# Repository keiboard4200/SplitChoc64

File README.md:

# SplitChoc64

SplitChoc64 is a 64-key split low-profile keyboard project built around Seeed XIAO nRF52840 and ZMK.

This repository contains firmware/software, PCB design, mechanical/3D-print data, manufacturing outputs, and project documentation.

## Repository layout

```text
SplitChoc64/
├─ hardware/                 # PCB, case, plate, trackball mechanical data and manufacturing files
│  ├─ main-pcb/
│  │  ├─ Ver000/
│  │  └─ Ver001/
│  └─ trackball-addon/
├─ software/                 # ZMK build/config/module source and archived firmware variants
│  ├─ build.yaml
│  ├─ west.yml
│  ├─ zmk-module/            # active Ver001 ZMK module
│  ├─ firmware/
│  │  ├─ joystick/           # legacy Ver000/2765 implementation
│  │  └─ trackball/          # Ver001 PAW3222 documentation
│  └─ tools/
├─ docs/                     # Project documentation
├─ archive/                  # Historical/original import data
├─ DEVELOPMENT/              # Development snapshots retained for traceability
├─ zephyr/module.yml         # Zephyr entry point redirecting to software/zmk-module
├─ .github/                  # GitHub Actions
└─ README.md
```

## Hardware baseline

- **Ver000**: first manufactured SplitChoc64 production hardware baseline (legacy internal name: Ver012).
- **Ver001**: current manufactured hardware/firmware baseline, stored under `hardware/main-pcb/Ver001/`.
- Kailh Choc V2 hot-swap switches.
- Seeed XIAO nRF52840 Plus on both halves.

## Active Ver001 pointing device

Ver001 uses the RIGHT-side PAW3222 trackball through the PCB-mounted 6-pin FFC interface. The active ZMK module under `software/zmk-module/` is configured for this hardware.

The older 2765 analog-joystick implementation is retained only as a legacy reference under `software/firmware/joystick/`; it is not compiled into the active Ver001 firmware.

Detailed Ver001 trackball wiring and firmware notes are in `software/firmware/trackball/README.md`.

## ZMK build

GitHub Actions reads:

- Build matrix: `software/build.yaml`
- West/config path: `software/`
- SplitChoc64 Zephyr/ZMK module: `software/zmk-module/`

`zephyr/module.yml` remains at repository root because ZMK/Zephyr module discovery expects the module entry point there. The implementation is organized under `software/`.

## Firmware identity

- Shield: `splitchoc64_left` / `splitchoc64_right`
- RIGHT: Central / USB-BLE host / PAW3222 trackball
- LEFT: Peripheral
- Bluetooth name: `SplitChoc64`
- ZMK Studio: retained
- `settings_reset` build: retained

## Validation status

GitHub Actions validates LEFT, RIGHT, and `settings_reset` builds. Physical PAW3222 direction, CPI and feel must still be tuned on the assembled Ver001 hardware.

## License

See the license files and upstream component licenses included with each subproject before redistribution or commercial use.

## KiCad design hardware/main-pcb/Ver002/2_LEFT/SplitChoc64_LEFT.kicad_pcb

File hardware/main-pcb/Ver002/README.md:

# SplitChoc64 Ver002

Clean GitHub source promoted from the user-reviewed XIAO nRF52840 Plus correction.

- `0_COMMON`: shared footprints / 3D assets
- `1_RIGHT`: RIGHT KiCad project + ERC/DRC reports
- `2_LEFT`: LEFT KiCad project + ERC/DRC reports
- `3_PLATE`: accepted TopPlate STEP files
- `4_CASE`: accepted BottomCase / BatteryLid / trackball mechanical STEP files
- Manufacturing exports are intentionally not carried forward from Ver001; regenerate them from Ver002 when needed.

Validation confirmed by the user in KiCad 9.0 before promotion: LEFT/RIGHT ERC 0/0 and DRC 0/0.

Ver002 corrects XIAO nRF52840 Plus pads 28/29, removes unverified pads 30/31, preserves the project-specific front-side solder access pads 32/33, and leaves Ver001 unchanged as historical source.

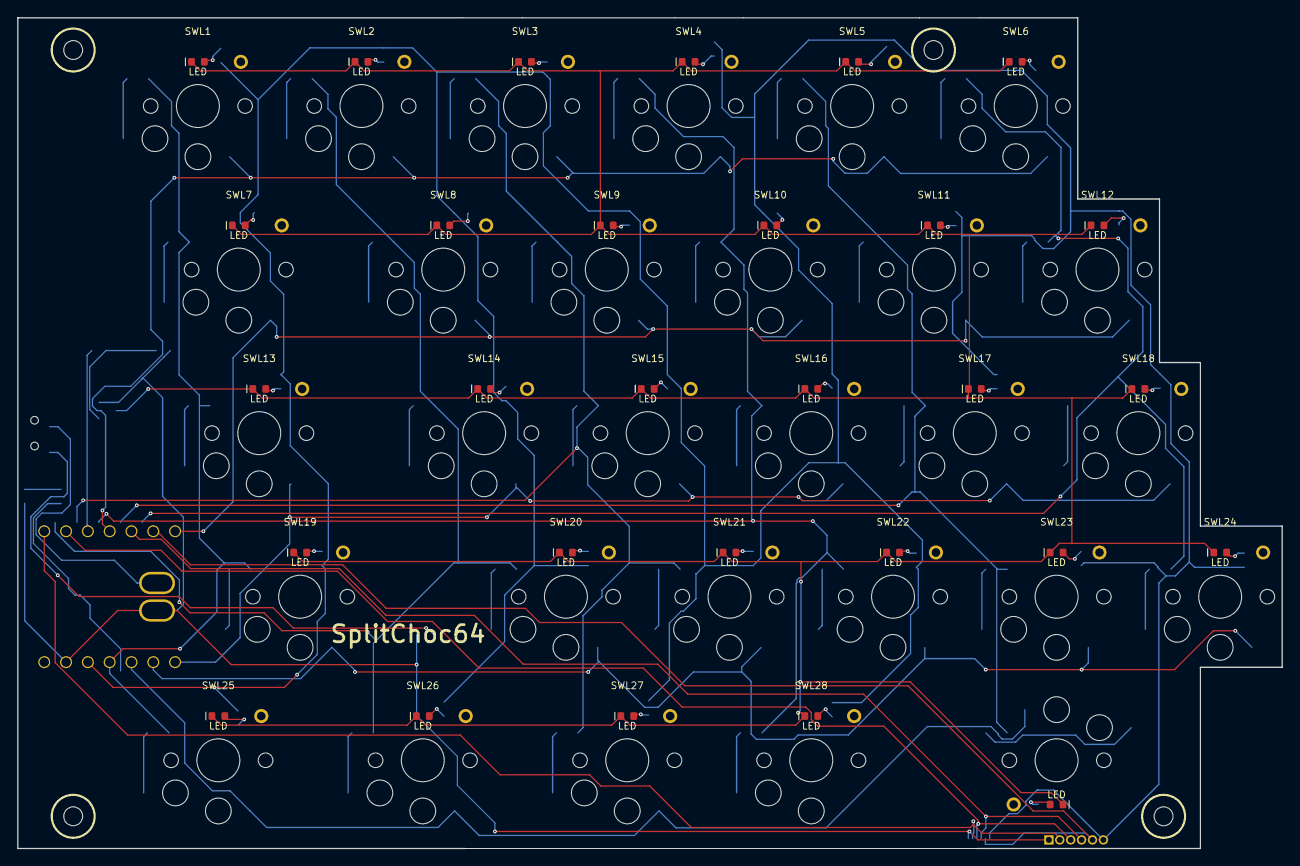
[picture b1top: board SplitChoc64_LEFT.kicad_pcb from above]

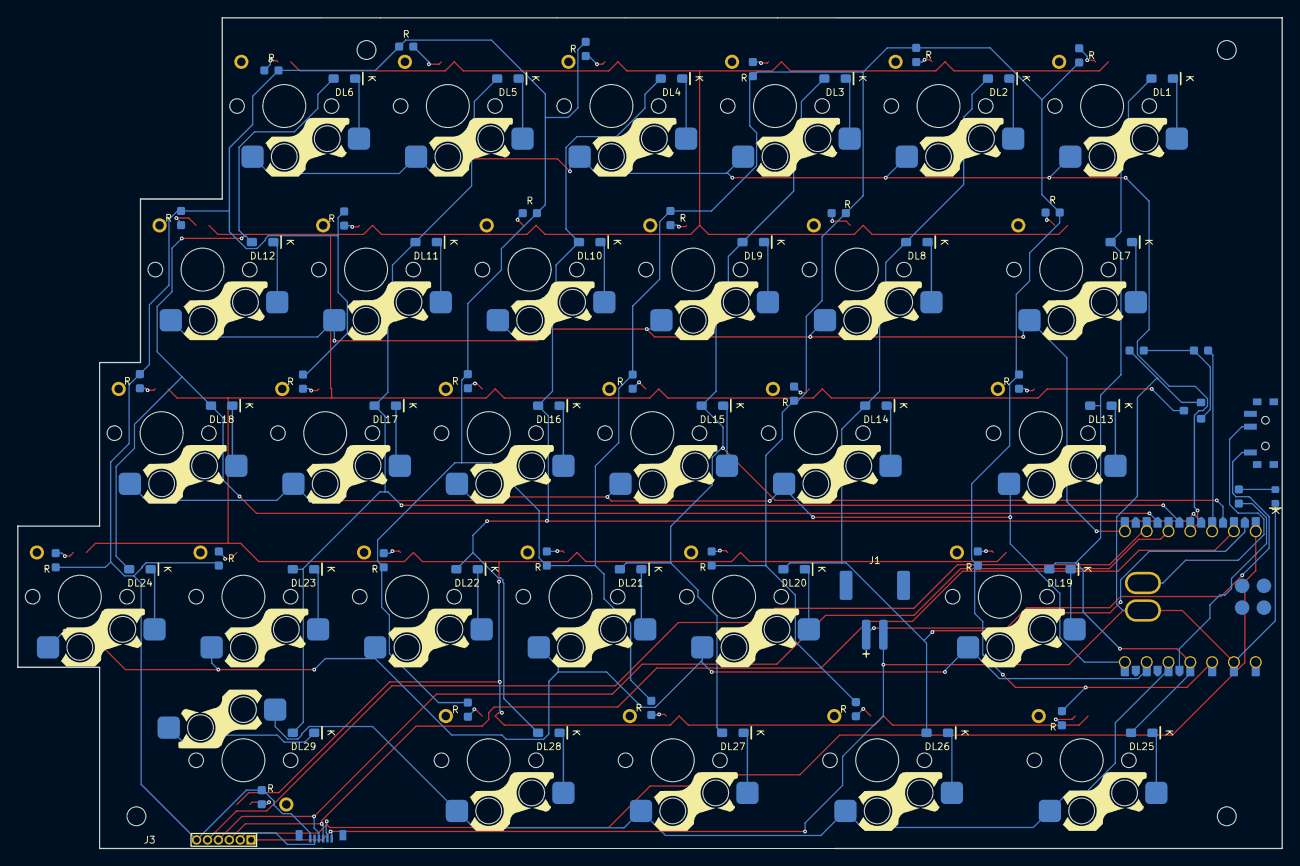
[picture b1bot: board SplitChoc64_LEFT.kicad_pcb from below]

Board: 2 copper layers, 147.3 x 96.8 mm, 130 parts (68 on the bottom side), 82 nets.

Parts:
DL1: 1N4148WS; DL1
DL2: 1N4148WS; DL2
DL3: 1N4148WS; DL3
DL4: 1N4148WS; DL4
DL5: 1N4148WS; DL5
DL6: 1N4148WS; DL6
DL7: 1N4148WS; DL7
DL8: 1N4148WS; DL8
DL9: 1N4148WS; DL9
DL10: 1N4148WS; DL10
DL11: 1N4148WS; DL11
DL12: 1N4148WS; DL12
DL13: 1N4148WS; DL13
DL14: 1N4148WS; DL14
DL15: 1N4148WS; DL15
DL16: 1N4148WS; DL16
DL17: 1N4148WS; DL17
DL18: 1N4148WS; DL18
DL19: 1N4148WS; DL19
DL20: 1N4148WS; DL20
DL21: 1N4148WS; DL21
DL22: 1N4148WS; DL22
DL23: 1N4148WS; DL23
DL24: 1N4148WS; DL24
DL25: 1N4148WS; DL25
DL26: 1N4148WS; DL26
DL27: 1N4148WS; DL27
DL28: 1N4148WS; DL28
DL29: 1N4148WS; DL29
DLED1: KT-0603B; LED_0603_TOP_BLUE
H1, H2, H3, H4: M2_CASE_MOUNT
J1: S2B-PH-SM4-TB; JST_PH_S2B-PH-SM4-TB_1x02-1MP_P2.00mm_Horizontal
J3: GND EXT_A EXT_B EXT_SDA EXT_SCL 3V3; J3
J5: FH19C-6S-0.5SH(10); FH19C-6S-0.5SH_HandSolder
LEDL1, LEDL2, LEDL3, LEDL4, LEDL5, LEDL6, LEDL7, LEDL8, LEDL9, LEDL10, LEDL11, LEDL12, LEDL13, LEDL14, LEDL15, LEDL16, LEDL17, LEDL18, LEDL19, LEDL20, LEDL21, LEDL22, LEDL23, LEDL24, LEDL25, LEDL26, LEDL27, LEDL28, LEDL29: SMLD12WBN1W1; SMLD12WBN1W1_0603
QBL1: 2N7002; SOT-23
RBLL1, RBLL2, RBLL3, RBLL4, RBLL5, RBLL6, RBLL7, RBLL8, RBLL9, RBLL10, RBLL11, RBLL12, RBLL13, RBLL14, RBLL15, RBLL16, RBLL17, RBLL18, RBLL19, RBLL20, RBLL21, RBLL22, RBLL23, RBLL24, RBLL25, RBLL26, RBLL27, RBLL28, RBLL29: 1k; STATUS_R_0603
RGBL1: 1k; STATUS_R_0603
RLED1: 100R; STATUS_R_0603
RPDL1: 100k; STATUS_R_0603
SWL1: Kailh Choc V2 / HotSwap; SWL1
SWL2: Kailh Choc V2 / HotSwap; SWL2
SWL3: Kailh Choc V2 / HotSwap; SWL3
SWL4: Kailh Choc V2 / HotSwap; SWL4
SWL5: Kailh Choc V2 / HotSwap; SWL5
SWL6: Kailh Choc V2 / HotSwap; SWL6
SWL7: Kailh Choc V2 / HotSwap; SWL7
SWL8: Kailh Choc V2 / HotSwap; SWL8
SWL9: Kailh Choc V2 / HotSwap; SWL9
SWL10: Kailh Choc V2 / HotSwap; SWL10
SWL11: Kailh Choc V2 / HotSwap; SWL11
SWL12: Kailh Choc V2 / HotSwap; SWL12
SWL13: Kailh Choc V2 / HotSwap; SWL13
SWL14: Kailh Choc V2 / HotSwap; SWL14
SWL15: Kailh Choc V2 / HotSwap; SWL15
SWL16: Kailh Choc V2 / HotSwap; SWL16
SWL17: Kailh Choc V2 / HotSwap; SWL17
SWL18: Kailh Choc V2 / HotSwap; SWL18
SWL19: Kailh Choc V2 / HotSwap; SWL19
SWL20: Kailh Choc V2 / HotSwap; SWL20
SWL21: Kailh Choc V2 / HotSwap; SWL21
SWL22: Kailh Choc V2 / HotSwap; SWL22
SWL23: Kailh Choc V2 / HotSwap; SWL23
SWL24: Kailh Choc V2 / HotSwap; SWL24
SWL25: Kailh Choc V2 / HotSwap; SWL25
SWL26: Kailh Choc V2 / HotSwap; SWL26
SWL27: Kailh Choc V2 / HotSwap; SWL27
SWL28: Kailh Choc V2 / HotSwap; SWL28
SWL29: Kailh Choc V2 / HotSwap; SWL29
SWP1: PCM12SMTR; SWP1
U1: XIAO nRF52840 Plus; U1

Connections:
L_3V3: J3.6, J5.6, RBLL1.1, RBLL2.1, RBLL3.1, RBLL4.1, RBLL5.1, RBLL6.1, RBLL7.1, RBLL8.1, RBLL9.1, RBLL10.1, RBLL11.1, RBLL12.1, RBLL13.1, RBLL14.1, RBLL15.1, RBLL16.1, RBLL17.1, RBLL18.1, RBLL19.1, RBLL20.1, RBLL21.1, RBLL22.1, RBLL23.1, RBLL24.1, RBLL25.1, RBLL26.1, RBLL27.1, RBLL28.1, RBLL29.1, U1.12
L_BAT_RAW: J1.1, SWP1.1
L_BAT_SW: SWP1.2, U1.28, U1.32
L_BL_GATE: QBL1.1, RGBL1.2, RPDL1.1
L_BL_LED_A1: LEDL1.2, RBLL1.2
L_BL_LED_A2: LEDL2.2, RBLL2.2
L_BL_LED_A3: LEDL3.2, RBLL3.2
L_BL_LED_A4: LEDL4.2, RBLL4.2
L_BL_LED_A5: LEDL5.2, RBLL5.2
L_BL_LED_A6: LEDL6.2, RBLL6.2
L_BL_LED_A7: LEDL7.2, RBLL7.2
L_BL_LED_A8: LEDL8.2, RBLL8.2
L_BL_LED_A9: LEDL9.2, RBLL9.2
L_BL_LED_A10: LEDL10.2, RBLL10.2
L_BL_LED_A11: LEDL11.2, RBLL11.2
L_BL_LED_A12: LEDL12.2, RBLL12.2
L_BL_LED_A13: LEDL13.2, RBLL13.2
L_BL_LED_A14: LEDL14.2, RBLL14.2
L_BL_LED_A15: LEDL15.2, RBLL15.2
L_BL_LED_A16: LEDL16.2, RBLL16.2
L_BL_LED_A17: LEDL17.2, RBLL17.2
L_BL_LED_A18: LEDL18.2, RBLL18.2
L_BL_LED_A19: LEDL19.2, RBLL19.2
L_BL_LED_A20: LEDL20.2, RBLL20.2
L_BL_LED_A21: LEDL21.2, RBLL21.2
L_BL_LED_A22: LEDL22.2, RBLL22.2
L_BL_LED_A23: LEDL23.2, RBLL23.2
L_BL_LED_A24: LEDL24.2, RBLL24.2
L_BL_LED_A25: LEDL25.2, RBLL25.2
L_BL_LED_A26: LEDL26.2, RBLL26.2
L_BL_LED_A27: LEDL27.2, RBLL27.2
L_BL_LED_A28: LEDL28.2, RBLL28.2
L_BL_LED_A29: LEDL29.2, RBLL29.2
L_BL_LED_RETURN: LEDL1.1, LEDL2.1, LEDL3.1, LEDL4.1, LEDL5.1, LEDL6.1, LEDL7.1, LEDL8.1, LEDL9.1, LEDL10.1, LEDL11.1, LEDL12.1, LEDL13.1, LEDL14.1, LEDL15.1, LEDL16.1, LEDL17.1, LEDL18.1, LEDL19.1, LEDL20.1, LEDL21.1, LEDL22.1, LEDL23.1, LEDL24.1, LEDL25.1, LEDL26.1, LEDL27.1, LEDL28.1, LEDL29.1, QBL1.3
L_BL_PWM: RGBL1.1, U1.3
L_COL0: DL1.2, DL7.2, DL13.2, DL19.2, DL25.2, U1.11
L_COL1: DL2.2, DL8.2, DL14.2, DL20.2, DL26.2, U1.15
L_COL2: DL3.2, DL9.2, DL15.2, DL21.2, DL27.2, U1.16
L_COL3: DL4.2, DL10.2, DL16.2, DL22.2, DL28.2, U1.17
L_COL4: DL5.2, DL11.2, DL17.2, DL23.2, DL29.2, U1.18
L_COL5: DL6.2, DL12.2, DL18.2, DL24.2, U1.19
L_EXT_A: J3.2, J5.2, U1.1
L_EXT_B: J3.3, J5.3, U1.2
L_EXT_SCL: J3.5, J5.5, U1.6
L_EXT_SDA: J3.4, J5.4, U1.5
L_GND: DLED1.1, J1.2, J3.1, J5.1, QBL1.2, RPDL1.2, U1.13, U1.29, U1.33
L_K1_D: DL1.1, SWL1.2
L_K2_D: DL2.1, SWL2.2
L_K3_D: DL3.1, SWL3.2
L_K4_D: DL4.1, SWL4.2
L_K5_D: DL5.1, SWL5.2
L_K6_D: DL6.1, SWL6.2
L_K7_D: DL7.1, SWL7.2
L_K8_D: DL8.1, SWL8.2
L_K9_D: DL9.1, SWL9.2
L_K10_D: DL10.1, SWL10.2
L_K11_D: DL11.1, SWL11.2
L_K12_D: DL12.1, SWL12.2
L_K13_D: DL13.1, SWL13.2
L_K14_D: DL14.1, SWL14.2
L_K15_D: DL15.1, SWL15.2
L_K16_D: DL16.1, SWL16.2
L_K17_D: DL17.1, SWL17.2
L_K18_D: DL18.1, SWL18.2
L_K19_D: DL19.1, SWL19.2
L_K20_D: DL20.1, SWL20.2
L_K21_D: DL21.1, SWL21.2
L_K22_D: DL22.1, SWL22.2
L_K23_D: DL23.1, SWL23.2
L_K24_D: DL24.1, SWL24.2
L_K25_D: DL25.1, SWL25.2
L_K26_D: DL26.1, SWL26.2
L_K27_D: DL27.1, SWL27.2
L_K28_D: DL28.1, SWL28.2
L_K29_D: DL29.1, SWL29.2
L_LED_A: DLED1.2, RLED1.2
L_LED_CTRL: RLED1.1, U1.23
L_ROW0: SWL1.1, SWL2.1, SWL3.1, SWL4.1, SWL5.1, SWL6.1, U1.4
L_ROW1: SWL7.1, SWL8.1, SWL9.1, SWL10.1, SWL11.1, SWL12.1, U1.7
L_ROW2: SWL13.1, SWL14.1, SWL15.1, SWL16.1, SWL17.1, SWL18.1, U1.8
L_ROW3: SWL19.1, SWL20.1, SWL21.1, SWL22.1, SWL23.1, SWL24.1, U1.9
L_ROW4: SWL25.1, SWL26.1, SWL27.1, SWL28.1, SWL29.1, U1.10

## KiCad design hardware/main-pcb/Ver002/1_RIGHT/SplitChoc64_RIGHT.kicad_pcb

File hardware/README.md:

# Hardware

This directory contains PCB source data, manufacturing outputs, and hardware-specific documentation.

## Main PCB

`main-pcb/Ver012/` is the frozen production baseline for the manufactured SplitChoc64 PCB.

Do not change:
- PCB outline
- key positions
- left/right interlocking geometry

## Trackball add-on

`trackball-addon/` contains the J4-to-FFC adapter PCB and associated manufacturing/mechanical data for the PAW3222/Torabo variant.

Where practical, keep editable source data and manufacturing outputs together and clearly versioned.

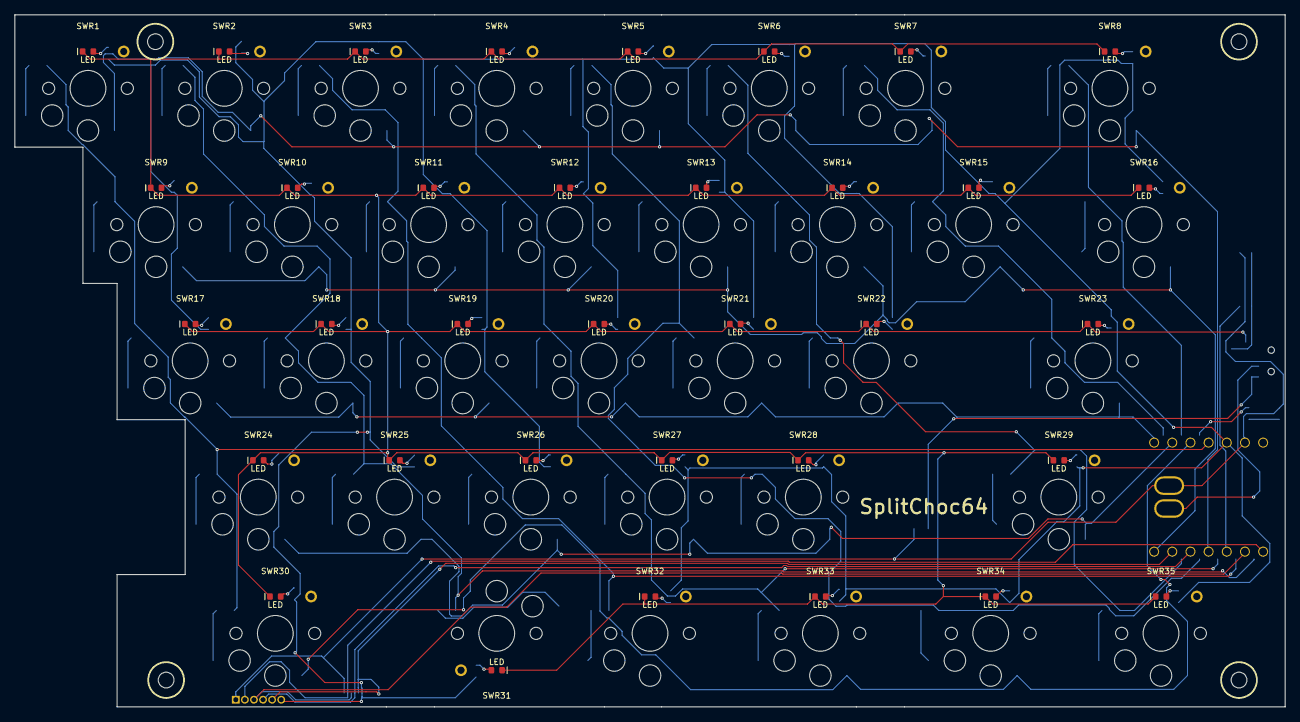
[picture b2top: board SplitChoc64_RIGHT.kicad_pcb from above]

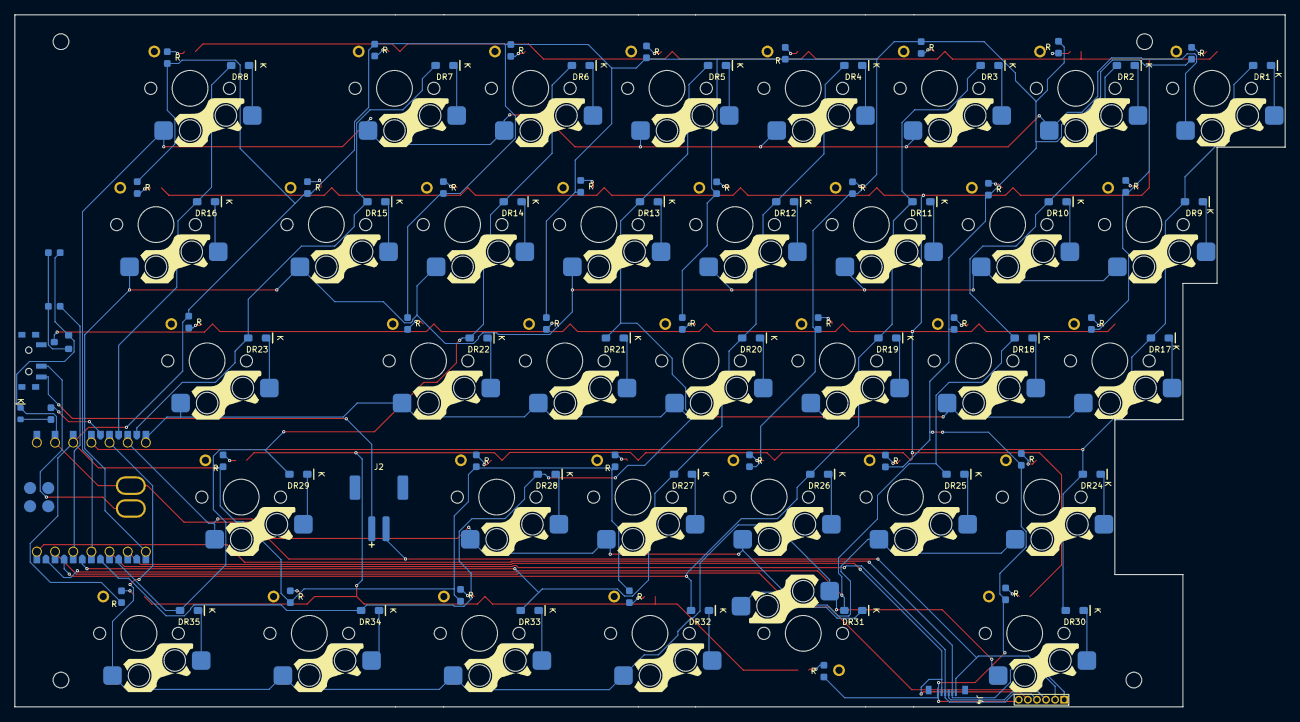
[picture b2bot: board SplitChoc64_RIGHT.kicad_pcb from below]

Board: 2 copper layers, 177.6 x 96.8 mm, 154 parts (80 on the bottom side), 96 nets.

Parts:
DLED2: KT-0603B; LED_0603_TOP_BLUE
DR1: 1N4148WS; DR1
DR2: 1N4148WS; DR2
DR3: 1N4148WS; DR3
DR4: 1N4148WS; DR4
DR5: 1N4148WS; DR5
DR6: 1N4148WS; DR6
DR7: 1N4148WS; DR7
DR8: 1N4148WS; DR8
DR9: 1N4148WS; DR9
DR10: 1N4148WS; DR10
DR11: 1N4148WS; DR11
DR12: 1N4148WS; DR12
DR13: 1N4148WS; DR13
DR14: 1N4148WS; DR14
DR15: 1N4148WS; DR15
DR16: 1N4148WS; DR16
DR17: 1N4148WS; DR17
DR18: 1N4148WS; DR18
DR19: 1N4148WS; DR19
DR20: 1N4148WS; DR20
DR21: 1N4148WS; DR21
DR22: 1N4148WS; DR22
DR23: 1N4148WS; DR23
DR24: 1N4148WS; DR24
DR25: 1N4148WS; DR25
DR26: 1N4148WS; DR26
DR27: 1N4148WS; DR27
DR28: 1N4148WS; DR28
DR29: 1N4148WS; DR29
DR30: 1N4148WS; DR30
DR31: 1N4148WS; DR31
DR32: 1N4148WS; DR32
DR33: 1N4148WS; DR33
DR34: 1N4148WS; DR34
DR35: 1N4148WS; DR35
J2: S2B-PH-SM4-TB; JST_PH_S2B-PH-SM4-TB_1x02-1MP_P2.00mm_Horizontal
J4: GND EXT_A EXT_B EXT_SDA EXT_SCL 3V3; J4
J6: FH19C-6S-0.5SH(10); FH19C-6S-0.5SH_HandSolder
LEDR1, LEDR2, LEDR3, LEDR4, LEDR5, LEDR6, LEDR7, LEDR8, LEDR9, LEDR10, LEDR11, LEDR12, LEDR13, LEDR14, LEDR15, LEDR16, LEDR17, LEDR18, LEDR19, LEDR20, LEDR21, LEDR22, LEDR23, LEDR24, LEDR25, LEDR26, LEDR27, LEDR28, LEDR29, LEDR30, LEDR31, LEDR32, LEDR33, LEDR34, LEDR35: SMLD12WBN1W1; SMLD12WBN1W1_0603
QBL2: 2N7002; SOT-23
RBLR1, RBLR2, RBLR3, RBLR4, RBLR5, RBLR6, RBLR7, RBLR8, RBLR9, RBLR10, RBLR11, RBLR12, RBLR13, RBLR14, RBLR15, RBLR16, RBLR17, RBLR18, RBLR19, RBLR20, RBLR21, RBLR22, RBLR23, RBLR24, RBLR25, RBLR26, RBLR27, RBLR28, RBLR29, RBLR30, RBLR31, RBLR32, RBLR33, RBLR34, RBLR35: 1k; STATUS_R_0603
RGBL2: 1k; STATUS_R_0603
RLED2: 100R; STATUS_R_0603
RPDR2: 100k; STATUS_R_0603
R_H1, R_H2, R_H3, R_H4: M2_CASE_MOUNT
SWP2: PCM12SMTR; SWP2
SWR1: Kailh Choc V2 / HotSwap; SWR1
SWR2: Kailh Choc V2 / HotSwap; SWR2
SWR3: Kailh Choc V2 / HotSwap; SWR3
SWR4: Kailh Choc V2 / HotSwap; SWR4
SWR5: Kailh Choc V2 / HotSwap; SWR5
SWR6: Kailh Choc V2 / HotSwap; SWR6
SWR7: Kailh Choc V2 / HotSwap; SWR7
SWR8: Kailh Choc V2 / HotSwap; SWR8
SWR9: Kailh Choc V2 / HotSwap; SWR9
SWR10: Kailh Choc V2 / HotSwap; SWR10
SWR11: Kailh Choc V2 / HotSwap; SWR11
SWR12: Kailh Choc V2 / HotSwap; SWR12
SWR13: Kailh Choc V2 / HotSwap; SWR13
SWR14: Kailh Choc V2 / HotSwap; SWR14
SWR15: Kailh Choc V2 / HotSwap; SWR15
SWR16: Kailh Choc V2 / HotSwap; SWR16
SWR17: Kailh Choc V2 / HotSwap; SWR17
SWR18: Kailh Choc V2 / HotSwap; SWR18
SWR19: Kailh Choc V2 / HotSwap; SWR19
SWR20: Kailh Choc V2 / HotSwap; SWR20
SWR21: Kailh Choc V2 / HotSwap; SWR21
SWR22: Kailh Choc V2 / HotSwap; SWR22
SWR23: Kailh Choc V2 / HotSwap; SWR23
SWR24: Kailh Choc V2 / HotSwap; SWR24
SWR25: Kailh Choc V2 / HotSwap; SWR25
SWR26: Kailh Choc V2 / HotSwap; SWR26
SWR27: Kailh Choc V2 / HotSwap; SWR27
SWR28: Kailh Choc V2 / HotSwap; SWR28
SWR29: Kailh Choc V2 / HotSwap; SWR29
SWR30: Kailh Choc V2 / HotSwap; SWR30
SWR31: Kailh Choc V2 / HotSwap; SWR31
SWR32: Kailh Choc V2 / HotSwap; SWR32
SWR33: Kailh Choc V2 / HotSwap; SWR33
SWR34: Kailh Choc V2 / HotSwap; SWR34
SWR35: Kailh Choc V2 / HotSwap; SWR35
U2: XIAO nRF52840 Plus; U2

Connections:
R_3V3: J4.6, J6.6, RBLR1.1, RBLR2.1, RBLR3.1, RBLR4.1, RBLR5.1, RBLR6.1, RBLR7.1, RBLR8.1, RBLR9.1, RBLR10.1, RBLR11.1, RBLR12.1, RBLR13.1, RBLR14.1, RBLR15.1, RBLR16.1, RBLR17.1, RBLR18.1, RBLR19.1, RBLR20.1, RBLR21.1, RBLR22.1, RBLR23.1, RBLR24.1, RBLR25.1, RBLR26.1, RBLR27.1, RBLR28.1, RBLR29.1, RBLR30.1, RBLR31.1, RBLR32.1, RBLR33.1, RBLR34.1, RBLR35.1, U2.12
R_BAT_RAW: J2.1, SWP2.3
R_BAT_SW: SWP2.2, U2.28, U2.32
R_BL_GATE: QBL2.1, RGBL2.2, RPDR2.1
R_BL_LED_A1: LEDR1.2, RBLR1.2
R_BL_LED_A2: LEDR2.2, RBLR2.2
R_BL_LED_A3: LEDR3.2, RBLR3.2
R_BL_LED_A4: LEDR4.2, RBLR4.2
R_BL_LED_A5: LEDR5.2, RBLR5.2
R_BL_LED_A6: LEDR6.2, RBLR6.2
R_BL_LED_A7: LEDR7.2, RBLR7.2
R_BL_LED_A8: LEDR8.2, RBLR8.2
R_BL_LED_A9: LEDR9.2, RBLR9.2
R_BL_LED_A10: LEDR10.2, RBLR10.2
R_BL_LED_A11: LEDR11.2, RBLR11.2
R_BL_LED_A12: LEDR12.2, RBLR12.2
R_BL_LED_A13: LEDR13.2, RBLR13.2
R_BL_LED_A14: LEDR14.2, RBLR14.2
R_BL_LED_A15: LEDR15.2, RBLR15.2
R_BL_LED_A16: LEDR16.2, RBLR16.2
R_BL_LED_A17: LEDR17.2, RBLR17.2
R_BL_LED_A18: LEDR18.2, RBLR18.2
R_BL_LED_A19: LEDR19.2, RBLR19.2
R_BL_LED_A20: LEDR20.2, RBLR20.2
R_BL_LED_A21: LEDR21.2, RBLR21.2
R_BL_LED_A22: LEDR22.2, RBLR22.2
R_BL_LED_A23: LEDR23.2, RBLR23.2
R_BL_LED_A24: LEDR24.2, RBLR24.2
R_BL_LED_A25: LEDR25.2, RBLR25.2
R_BL_LED_A26: LEDR26.2, RBLR26.2
R_BL_LED_A27: LEDR27.2, RBLR27.2
R_BL_LED_A28: LEDR28.2, RBLR28.2
R_BL_LED_A29: LEDR29.2, RBLR29.2
R_BL_LED_A30: LEDR30.2, RBLR30.2
R_BL_LED_A31: LEDR31.2, RBLR31.2
R_BL_LED_A32: LEDR32.2, RBLR32.2
R_BL_LED_A33: LEDR33.2, RBLR33.2
R_BL_LED_A34: LEDR34.2, RBLR34.2
R_BL_LED_A35: LEDR35.2, RBLR35.2
R_BL_LED_RETURN: LEDR1.1, LEDR2.1, LEDR3.1, LEDR4.1, LEDR5.1, LEDR6.1, LEDR7.1, LEDR8.1, LEDR9.1, LEDR10.1, LEDR11.1, LEDR12.1, LEDR13.1, LEDR14.1, LEDR15.1, LEDR16.1, LEDR17.1, LEDR18.1, LEDR19.1, LEDR20.1, LEDR21.1, LEDR22.1, LEDR23.1, LEDR24.1, LEDR25.1, LEDR26.1, LEDR27.1, LEDR28.1, LEDR29.1, LEDR30.1, LEDR31.1, LEDR32.1, LEDR33.1, LEDR34.1, LEDR35.1, QBL2.3
R_BL_PWM: RGBL2.1, U2.3
R_COL0: DR1.2, DR9.2, DR17.2, DR24.2, DR30.2, U2.11
R_COL1: DR2.2, DR10.2, DR18.2, DR25.2, DR31.2, U2.15
R_COL2: DR3.2, DR11.2, DR19.2, DR26.2, DR32.2, U2.16
R_COL3: DR4.2, DR12.2, DR20.2, DR27.2, DR33.2, U2.17
R_COL4: DR5.2, DR13.2, DR21.2, DR28.2, DR34.2, U2.18
R_COL5: DR6.2, DR14.2, DR22.2, DR29.2, DR35.2, U2.19
R_COL6: DR7.2, DR15.2, DR23.2, U2.21
R_COL7: DR8.2, DR16.2, U2.22
R_EXT_A: J4.2, J6.2, U2.1
R_EXT_B: J4.3, J6.3, U2.2
R_EXT_SCL: J4.5, J6.5, U2.6
R_EXT_SDA: J4.4, J6.4, U2.5
R_GND: DLED2.1, J2.2, J4.1, J6.1, QBL2.2, RPDR2.2, U2.13, U2.29, U2.33
R_K1_D: DR1.1, SWR1.2
R_K2_D: DR2.1, SWR2.2
R_K3_D: DR3.1, SWR3.2
R_K4_D: DR4.1, SWR4.2
R_K5_D: DR5.1, SWR5.2
R_K6_D: DR6.1, SWR6.2
R_K7_D: DR7.1, SWR7.2
R_K8_D: DR8.1, SWR8.2
R_K9_D: DR9.1, SWR9.2
R_K10_D: DR10.1, SWR10.2
R_K11_D: DR11.1, SWR11.2
R_K12_D: DR12.1, SWR12.2
R_K13_D: DR13.1, SWR13.2
R_K14_D: DR14.1, SWR14.2
R_K15_D: DR15.1, SWR15.2
R_K16_D: DR16.1, SWR16.2
R_K17_D: DR17.1, SWR17.2
R_K18_D: DR18.1, SWR18.2
R_K19_D: DR19.1, SWR19.2
R_K20_D: DR20.1, SWR20.2
R_K21_D: DR21.1, SWR21.2
R_K22_D: DR22.1, SWR22.2
R_K23_D: DR23.1, SWR23.2
R_K24_D: DR24.1, SWR24.2
R_K25_D: DR25.1, SWR25.2
R_K26_D: DR26.1, SWR26.2
R_K27_D: DR27.1, SWR27.2
R_K28_D: DR28.1, SWR28.2
R_K29_D: DR29.1, SWR29.2
R_K30_D: DR30.1, SWR30.2
R_K31_D: DR31.1, SWR31.2
R_K32_D: DR32.1, SWR32.2
R_K33_D: DR33.1, SWR33.2
R_K34_D: DR34.1, SWR34.2
R_K35_D: DR35.1, SWR35.2
R_LED_A: DLED2.2, RLED2.2
R_LED_CTRL: RLED2.1, U2.23
R_ROW0: SWR1.1, SWR2.1, SWR3.1, SWR4.1, SWR5.1, SWR6.1, SWR7.1, SWR8.1, U2.4
R_ROW1: SWR9.1, SWR10.1, SWR11.1, SWR12.1, SWR13.1, SWR14.1, SWR15.1, SWR16.1, U2.7
R_ROW2: SWR17.1, SWR18.1, SWR19.1, SWR20.1, SWR21.1, SWR22.1, SWR23.1, U2.8
R_ROW3: SWR24.1, SWR25.1, SWR26.1, SWR27.1, SWR28.1, SWR29.1, U2.9
R_ROW4: SWR30.1, SWR31.1, SWR32.1, SWR33.1, SWR34.1, SWR35.1, U2.10
